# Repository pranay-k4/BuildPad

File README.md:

# BuildPad
BuildPad is customizable macro pad with OLED display, layers, media controls and more.

## Why BuildPad?
BuildPad is customizable open-source macropad for makers, coders, designers, and electronics builders and why I made this because building something yourself is way more fun than buying it and I love hardware.

## Features
- 6 programmable mechanical keys
- Rotary encoder
- OLED display
- RGB lighting
- Custom firmware
- Open-source hardware
- Bongo Cat animation

## CAD Render

## PCB Screenshots

## Hardware
- XIAO RP2040
- SSD1306 128×32 OLED
- MX Cherry Switches
- SK6812 MINI E Leds
- EC11 Rotary Encoder

## Build Your Own BuildPad

### 1. Order the PCB
Export the Gerber files from the PCB folder and order the board from your preferred PCB manufacturer.

### 2. Print the Case
Print the top and bottom case parts using the files in the case directory.

[CAD Source](https://cad.onshape.com/documents/56e50c354be83b1f527c4f36/w/ea902eb5d511072ea0b73db3/e/02ae305e326d8373da2c26ce?renderMode=0&uiState=6a47eb012f119bc675f6dd9a)

### 3. Gather Components
Use the BOM to source all required components.

### 4. Assemble the PCB
Solder:
1. Diodes
2. RGB LEDs
3. XIAO RP2040
4. OLED Display
5. Rotary Encoder
6. Mechanical Switches

### 5. Install Heat Set Inserts
Install M2 heat-set inserts into the top case.

### 6. Flash Firmware
Install QMK and compile:
```bash
qmk compile -kb buildpad -km default
```
Flash the generated firmware onto the XIAO RP2040.

### 7. Assemble the Case
Mount the PCB inside the case and secure everything using M2 screws.

## BOM
# Bill of Materials

| Item | Qty | Component | Specification | Price | Link |
|------|-----|------------|---------------|--------|------|
| 1 | 1 | Microcontroller | Seeed Studio XIAO RP2040 | ~$6-7 | https://robu.in/product/seeed-studio-xiao-rp2040-v1-0/ |
| 2 | 1 | OLED Display | 0.91in SSD1306 I2C OLED (128x32) | ~$2.5 | https://robu.in/product/0-91-inch-128x32-i2c-iic-serial-blue-oled-lcd-display-module/ |
| 3 | 1 | Rotary Encoder | EC11 Encoder with Push Switch | ~$0.6 | https://robu.in/product/hongyan-ec11h-7ce20p1zy20-rotary-encoder-with-push-button-switch-vertical-plug-in-5-pin/ |
| 4 | 1 | Mechanical Switches | Cherry MX Compatible Switches (Pack of 10) | ~$4 | https://meckeys.com/shop/accessories/keyboard-accessories/key-switches/cherry-mx-rgb-switch/ |
| 5 | 2 | Keycaps | MX Compatible Keycaps (Pack of 5) | ~$2 | https://meckeys.com/shop/accessories/keyboard-accessories/keycaps/blank/blank-dsa-keycaps-1u/ |
| 6 | 8 | RGB LEDs | SK6812MINI-E Reverse Mount RGB LEDs | ~$3 | https://www.lcsc.com/product-detail/C5149201.html |
| 7 | 6 | Diodes | 1N4148W SOD-123 | ~$0.5 | https://www.lcsc.com/product-detail/C81598.html |
| 8 | 1 | PCB | BuildPad v1 PCB | $4 + $8 shipping | JLCPCB |
| 9 | 1 | Case | BuildPad v1 3D Printed Case | - | - |
| 10 | 8 | Heat Set Inserts | M2 Brass Heat Set Inserts | ~$1.5 | https://robu.in/product/m2-x-4-mm-brass-insert/ |
| 11 | 4 | Screws | M2 Machine Screws 12mm Long | ~$0.5 | https://robu.in/product/easymech-m2-x-12mm-hex-allen-csk-high-tensile109-black-oxide-screw-dia-2mm-length-12mm/ |
| 12 | 4 | Screws | M2 Machine Screws 4mm Long | ~$0.5 | TBD |
| 13 | 1 | Encoder Knob | 6mm Shaft Encoder Knob | ~$1 | TBD |

## License
This project is licensed under the MIT License.

## Author
Pranay Kamle

BuildPad v1 • 2026

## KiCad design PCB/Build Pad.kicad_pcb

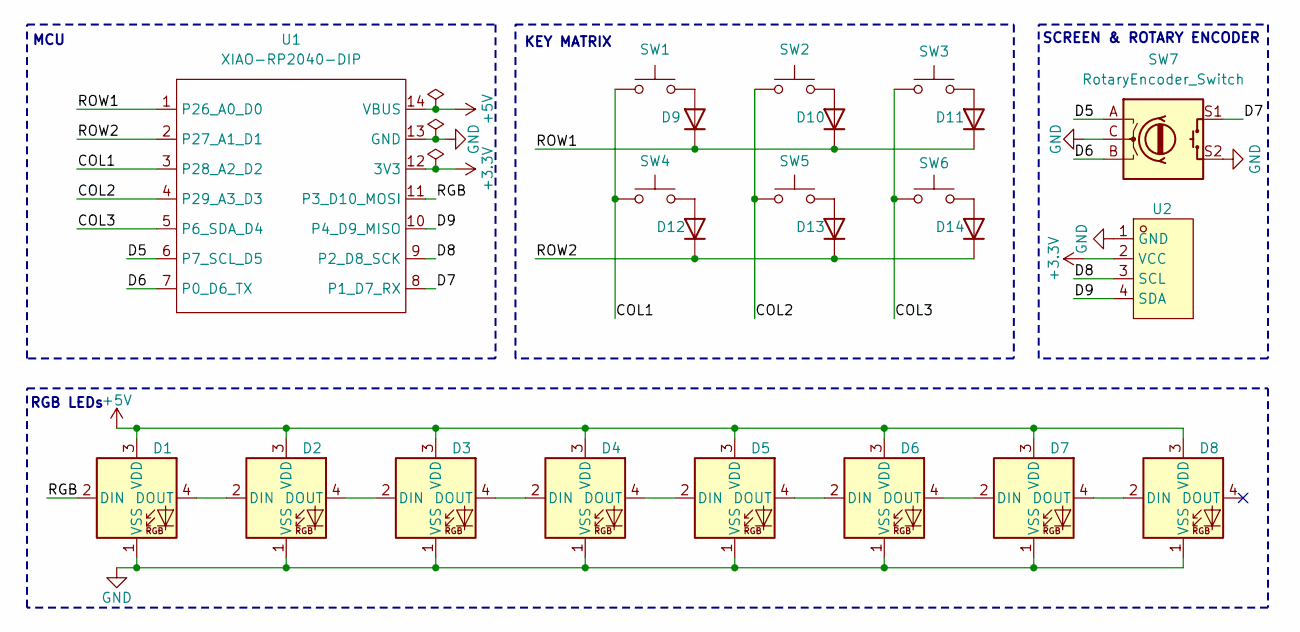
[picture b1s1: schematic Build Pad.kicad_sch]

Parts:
D1, D2, D3, D4, D5, D6, D7, D8: SK6812MINI-E; LED_SK6812MINI-E_3.2x2.8mm_P1.5mm_ReverseMount
D9, D10, D11, D12, D13, D14: 1N4148; D_SOD-123
SW1, SW2, SW3, SW4, SW5, SW6: SW_Push; SW_Cherry_MX_1.00u_PCB
SW7: RotaryEncoder_Switch; RotaryEncoder_Alps_EC11E-Switch_Vertical_H20mm_CircularMoun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
U1: XIAO-RP2040-DIP
U2: HS96L03W2C03; OLED-TH_L27.8-W27.2-P2.54_C9900033791; MPN HS96L03W2C03; LCSC Part C5248080

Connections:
+3.3V: U1.12 (3V3), U2.2 (VCC); also elsewhere on the board
+5V: D1.3 (VDD), D2.3 (VDD), D3.3 (VDD), D4.3 (VDD), D5.3 (VDD), D6.3 (VDD), D7.3 (VDD), D8.3 (VDD), U1.14 (VBUS)
/COL1: SW1.1, SW4.1, U1.3 (P28_A2_D2)
/COL2: SW2.1, SW5.1, U1.4 (P29_A3_D3)
/COL3: SW3.1, SW6.1, U1.5 (P6_SDA_D4)
/D5: SW7.A, U1.6 (P7_SCL_D5)
/D6: SW7.B, U1.7 (P0_D6_TX)
/D7: SW7.S1, U1.8 (P1_D7_RX)
/D8: U1.9 (P2_D8_SCK), U2.3 (SCL); also elsewhere on the board
/D9: U1.10 (P4_D9_MISO), U2.4 (SDA); also elsewhere on the board
/RGB: D1.2 (DIN), U1.11 (P3_D10_MOSI)
/ROW1: D9.1 (K), D10.1 (K), D11.1 (K), U1.1 (P26_A0_D0)
/ROW2: D12.1 (K), D13.1 (K), D14.1 (K), U1.2 (P27_A1_D1)
GND: D1.1 (VSS), D2.1 (VSS), D3.1 (VSS), D4.1 (VSS), D5.1 (VSS), D6.1 (VSS), D7.1 (VSS), D8.1 (VSS), SW7.C, SW7.S2, U1.13 (GND), U2.1 (GND); also elsewhere on the board
unnamed: D1.4 (DOUT), D2.2 (DIN)
unnamed: D2.4 (DOUT), D3.2 (DIN)
unnamed: D3.4 (DOUT), D4.2 (DIN)
unnamed: D4.4 (DOUT), D5.2 (DIN)
unnamed: D5.4 (DOUT), D6.2 (DIN)
unnamed: D6.4 (DOUT), D7.2 (DIN)
unnamed: D7.4 (DOUT), D8.2 (DIN)
unnamed: D9.2 (A), SW1.2
unnamed: D10.2 (A), SW2.2
unnamed: D11.2 (A), SW3.2
unnamed: D12.2 (A), SW4.2
unnamed: D13.2 (A), SW5.2
unnamed: D14.2 (A), SW6.2

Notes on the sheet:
MCU
RGB LEDs
SCREEN & ROTARY ENCODER
KEY MATRIX

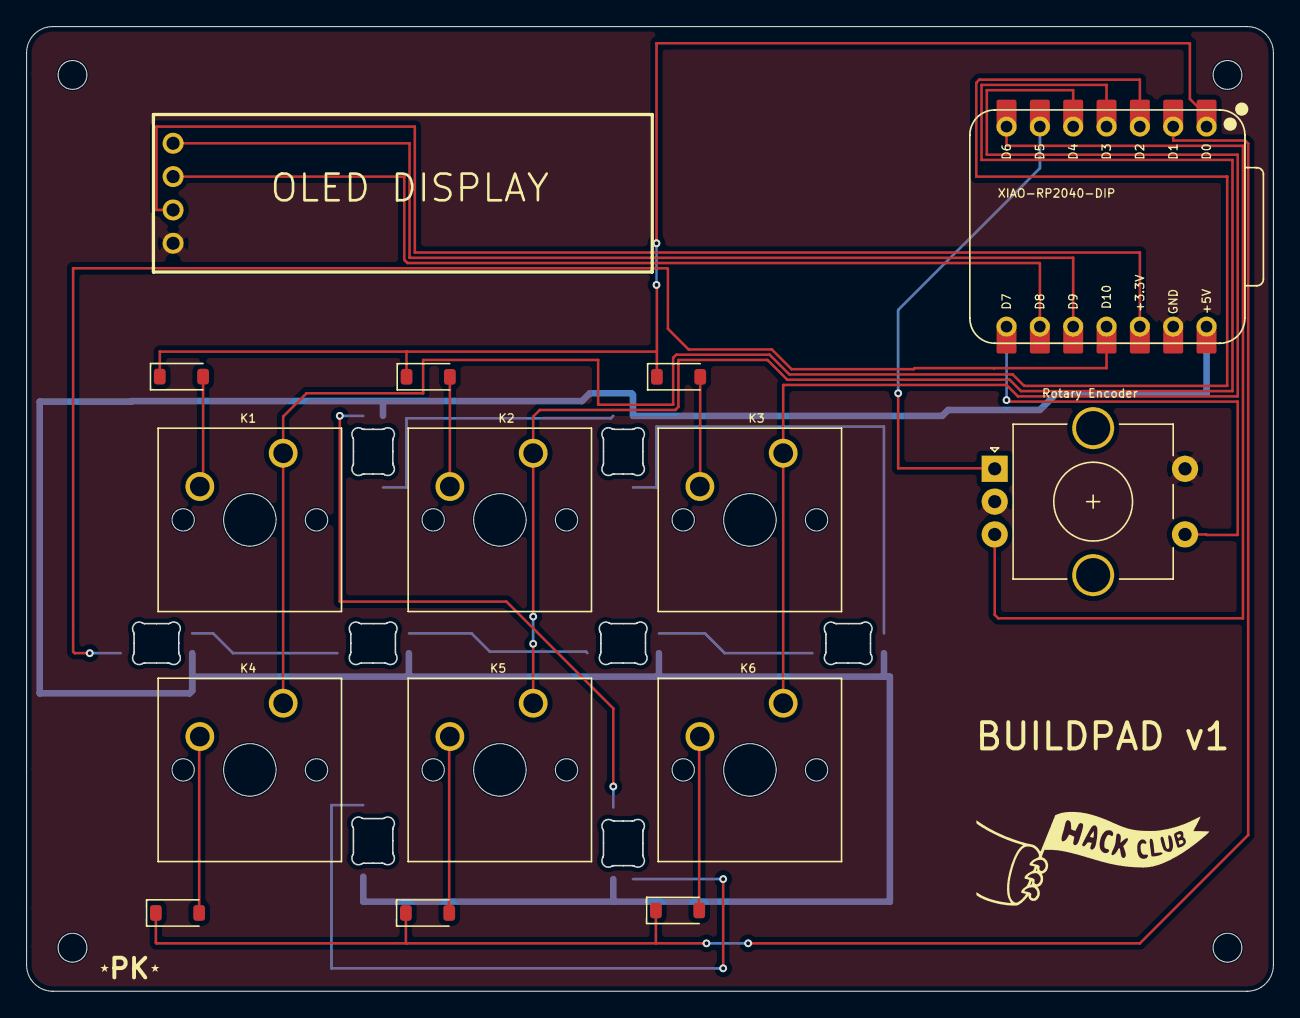
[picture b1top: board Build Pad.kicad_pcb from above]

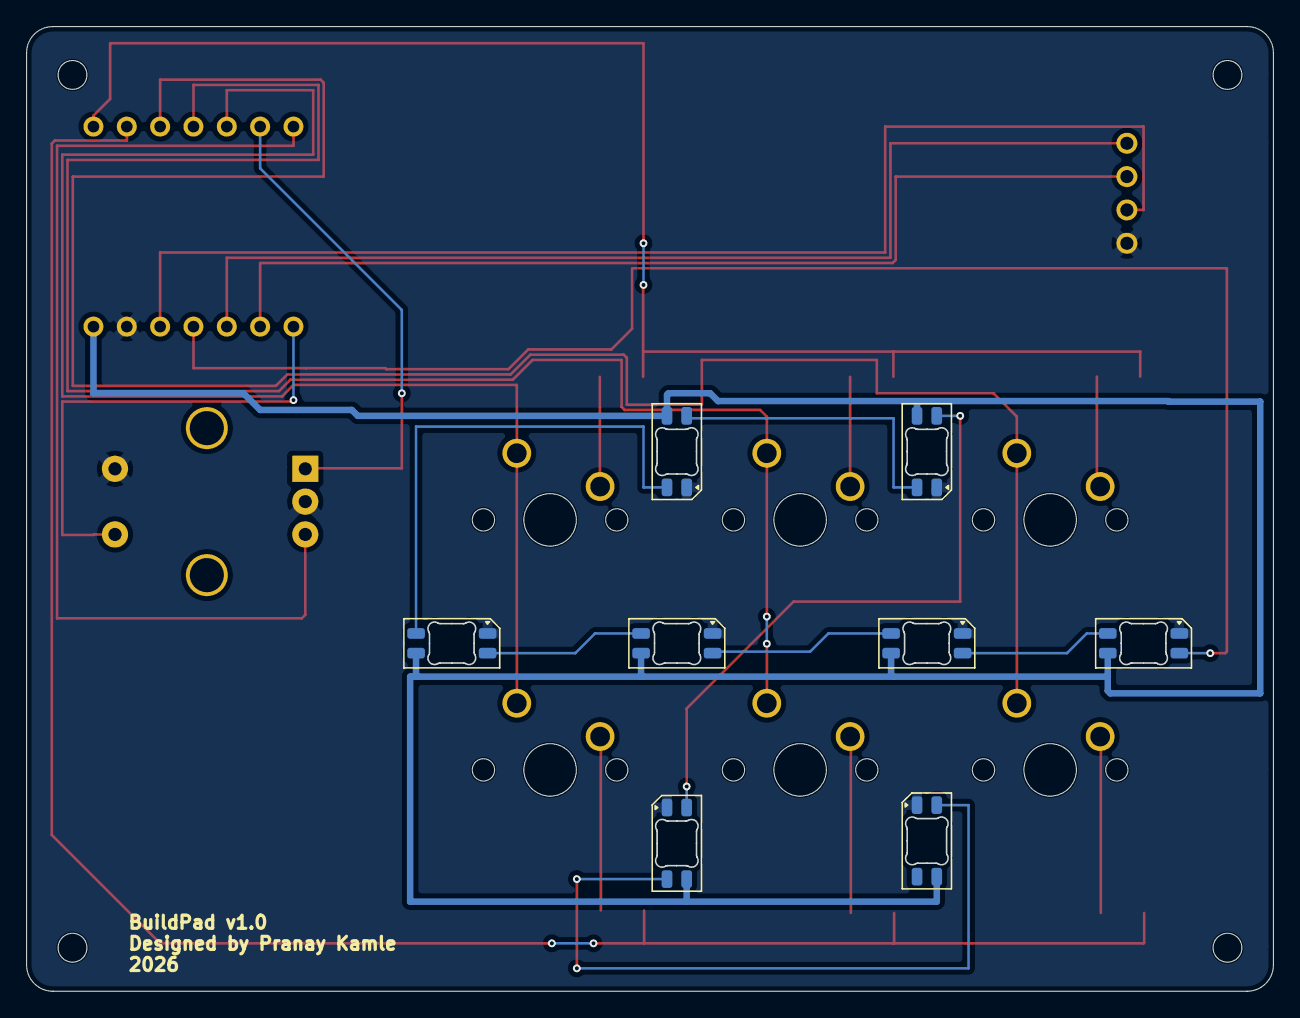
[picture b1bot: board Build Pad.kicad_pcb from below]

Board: 2 copper layers, 94.9 x 73.4 mm, 23 parts (8 on the bottom side), 27 nets.

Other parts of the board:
OLED1: HS91L02W2C01; OLED-TH_L38.0-W12.0_HS91L02W2C01

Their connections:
+3.3V: OLED1.2 (VCC); also elsewhere on the board
/D8: OLED1.3 (SCL); also elsewhere on the board
/D9: OLED1.4 (SDA); also elsewhere on the board
GND: OLED1.1 (GND); also elsewhere on the board

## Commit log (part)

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2026-06-14 Rename Build Pad.kicad_sch to PCB/Build Pad.kicad_sch
2026-06-17 Rename BuildPad v1.zip to PCB/BuildPad v1.zip
2026-06-23 Rename BuildPad v1 Final.zip to BuildPad v1 (Gerbers).zip
